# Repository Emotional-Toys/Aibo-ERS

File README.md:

## Aibo-ERS

Research repo for our work with ideal and the Sony Aibo ERS-210 and ERS-7.

### What is here

* Battery-cell [build](/battery-cell/README.md) build for the ERS-210.
* Battery-data [reader](/battery-reader/README.md) for the firmware aspect.
* Battery-state [monitor](/battery-monitor/README.md) for knowing everything you can about power.

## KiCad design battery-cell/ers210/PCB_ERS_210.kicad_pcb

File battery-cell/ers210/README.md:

## The retooling of the project

Here are the newly generated files.

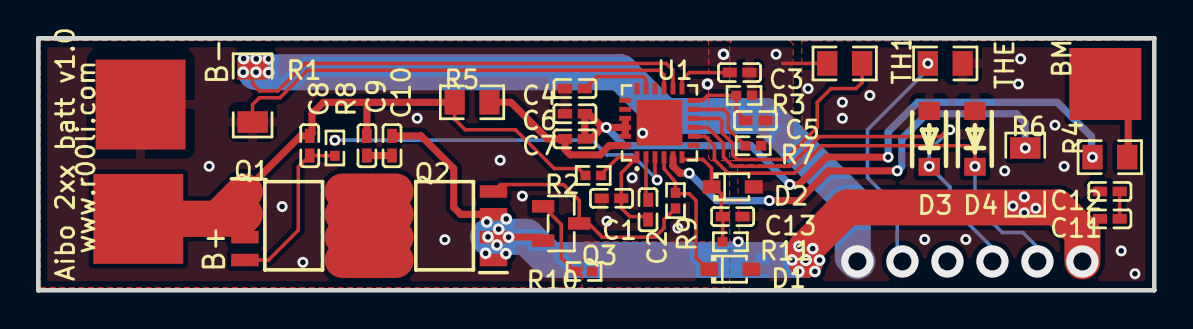
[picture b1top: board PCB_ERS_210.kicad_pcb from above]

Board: 2 copper layers, 62.0 x 14.0 mm, 37 parts (0 on the bottom side), 26 nets.

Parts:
B+: BATT+; PAD-1X-5X5MM
B-: BATT-; PAD-1X-5X5MM
BM: BATTM; PAD-1X-5X5MM
C1, C8, C9, C10, C11, C12: 0.1uF; C0402
C2, C3, C4, C5: 0.47uF; C0402
C6, C7, C13: 0.01uF; C0402
D1: SD101BW-7-F; SOD-323_L1.8-W1.3-LS2.5-RD
D2: SD103AWS-E3-08; SOD-323_L1.8-W1.3-LS2.5-RD
D3, D4: BZT52H-B5V6,115; SOD-123F_L2.8-W1.8-LS3.7-RD
Q1, Q2: IRF8714TRPBF; SOIC127P600X175-8N
Q3: 2N7002; SOT-23-3_L2.9-W1.3-P1.90-LS2.4-BR
R1: 0.005; R1206
R2: 10; R0402
R3, R10: 10k; R0402
R4, R5: 49.9; R0805
R6: 2k; R1206
R7, R11: 1k; R0402
R8, R9: 100; R0402
TH1: NTC 100k; R0805
THE: NTC 100k; R0805
U1: MAX17320G22+; QFN-24_L4.0-W4.0-P0.50-BL-EP2.6

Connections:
BATTM: BM.1, R4.2
BATTN: B-.1, C1.2, C3.1, C4.1, C5.2, C6.1, R1.2, R3.1, R7.1, TH1.1, U1.20, U1.25
BATTP: B+.1, C8.2, C9.2, Q1.1, Q1.2, Q1.3, R2.1, R5.2
C9_1: C9.1, C10.2
C11_2: C11.2, C12.1
CHG: R8.1, U1.3
DIS: D1.1, R9.1, U1.4
OUT_BATTN: C12.2, C13.2, D1.2, D2.2, D3.2, D4.2, R1.1, R10.1, THE.1
OUT_BATTP: C10.1, C11.1, Q2.1, Q2.2, Q2.3, Q3.2, R6.1, R11.2
PCKP: C13.1, D2.1, R11.1, U1.6
PFAIL: R7.2, U1.11
Q1_4: C8.1, Q1.4, R8.2
Q1_8: Q1.5, Q1.6, Q1.7, Q1.8, Q2.5, Q2.6, Q2.7, Q2.8
Q2_4: Q2.4, Q3.3, R9.2
Q3_1: Q3.1, R10.2
SCL: D4.1, U1.8
SDA: D3.1, U1.9
TH1: TH1.2, U1.10
U1_1: C1.1, C2.2, R2.2, U1.1
U1_2: C2.1, U1.2
U1_5: R6.2, U1.5
U1_12: C5.1, R3.2, U1.12
U1_13: C3.2, U1.13
U1_17: C4.2, U1.17
U1_21: C6.2, C7.2, R4.1, U1.21, U1.22, U1.23
U1_24: C7.1, R5.1, U1.24

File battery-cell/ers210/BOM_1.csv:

ID,Name,Designator,Footprint,Quantity,Note,Purchase link
1,0.1uF,"C1,C8,C9,C10,C11,C12",C0402,6,25V,https://si.farnell.com/samsung-electro-mechanics/cl05a104ka5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
2,0.47uF,"C2,C3,C4,C5",C0402,4,25V,https://si.farnell.com/tdk/c1005x5r1v474k050bc/cap-0-47uf-35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
4,0.01uF,"C6,C7,C13",C0402,3,50V,https://si.farnell.com/samsung-electro-mechanics/cl05b103kb5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
6,SD101CWS-7-F,D1,SOD-323,1,,https://si.farnell.com/diodes-inc/sd101cws-7-f/diode-schottk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
7,SD103BWS,D2,SOD-323,1,,https://si.farnell.com/diodes-inc/sd103bwsq-7-f/schottky-dio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
8,"BZT52H-B5V6,115","D3,D4",SOD-123F,2,,https://si.farnell.com/nexperia/bzt52h-b5v6-115/diode-zener-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
9,IRF7490TRPBF,"Q1,Q2",SOIC,2,,https://si.farnell.com/infineon/irf7490trpbf/mosfet-n-ch-100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
10,2N7002,Q3,SOT-23-3,1,,https://si.farnell.com/nexperia/2n7002nxbkr/mosfet-n-ch-60v-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
11,0.005,R1,R1206,1,,https://si.farnell.com/tt-electronics-welwyn/mfc1206-r005ft5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
12,10,R2,R0402,1,,https://si.farnell.com/koa-speer-electronics/rk73b1ettp100j/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
13,10k,"R3,R10",R0402,2,,https://si.farnell.com/yageo/rc0402jr-0710kl/res-10k-5-0-062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
14,49.9,"R4,R5",R0805,2,,https://si.farnell.com/vishay/crcw080549r9fkea/res-49r9-1-0-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
15,2k,R6,R1206,1,0.25W,https://si.farnell.com/vishay/rcc12062k00fkea/res-2k-1-0-5w-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
16,1k,"R7,R11",R0402,2,,https://si.farnell.com/yageo/rc0402jr-071kl/res-1k-5-0-0625w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
17,100,"R8,R9",R0402,2,,https://si.farnell.com/yageo/rc0402jr-07100rl/res-100r-5-0-0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
18,NTC 100k,"R12,R13",R0805,2,NOT USED,https://si.farnell.com/epcos/b57164k0104j000/thermistor-ntc/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
19,MAX17320G20+,U1,QFN-24,1,,https://si.farnell.com/maxim-integrated-products/max17320g20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
20,Laptop battery connector,U2,"6 PIN, 2.5mm",1,Generic,https://www.aliexpress.com/item/32894485710.html

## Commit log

2025-02-08 Initial version
2025-02-08 Add index
2025-02-08 Add reader
2025-02-08 Add battery monitor
2025-02-08 Add datasheet
2025-02-08 Reveal installer
2025-02-08 Add maxim installer
2025-02-10 Add image
2025-02-10 Add aesthetic area
2025-02-10 Add designs
2025-02-10 Add driver link
2025-02-12 Add Sony research
2025-02-13 Edit
2025-02-14 Add challenge
2025-02-14 Add note
2025-02-24 Limit scope
2025-02-26 Add literature
2025-02-26 Add errata
2025-02-26 Add generated file
2025-02-26 Try export
2025-02-26 remove shit
2025-02-26 Add good bom
2025-02-27 Add mod
